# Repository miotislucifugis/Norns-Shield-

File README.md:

A (very minor) rework of Norns Shield 210330 that adds TRS (type A) Midi IN and OUT.

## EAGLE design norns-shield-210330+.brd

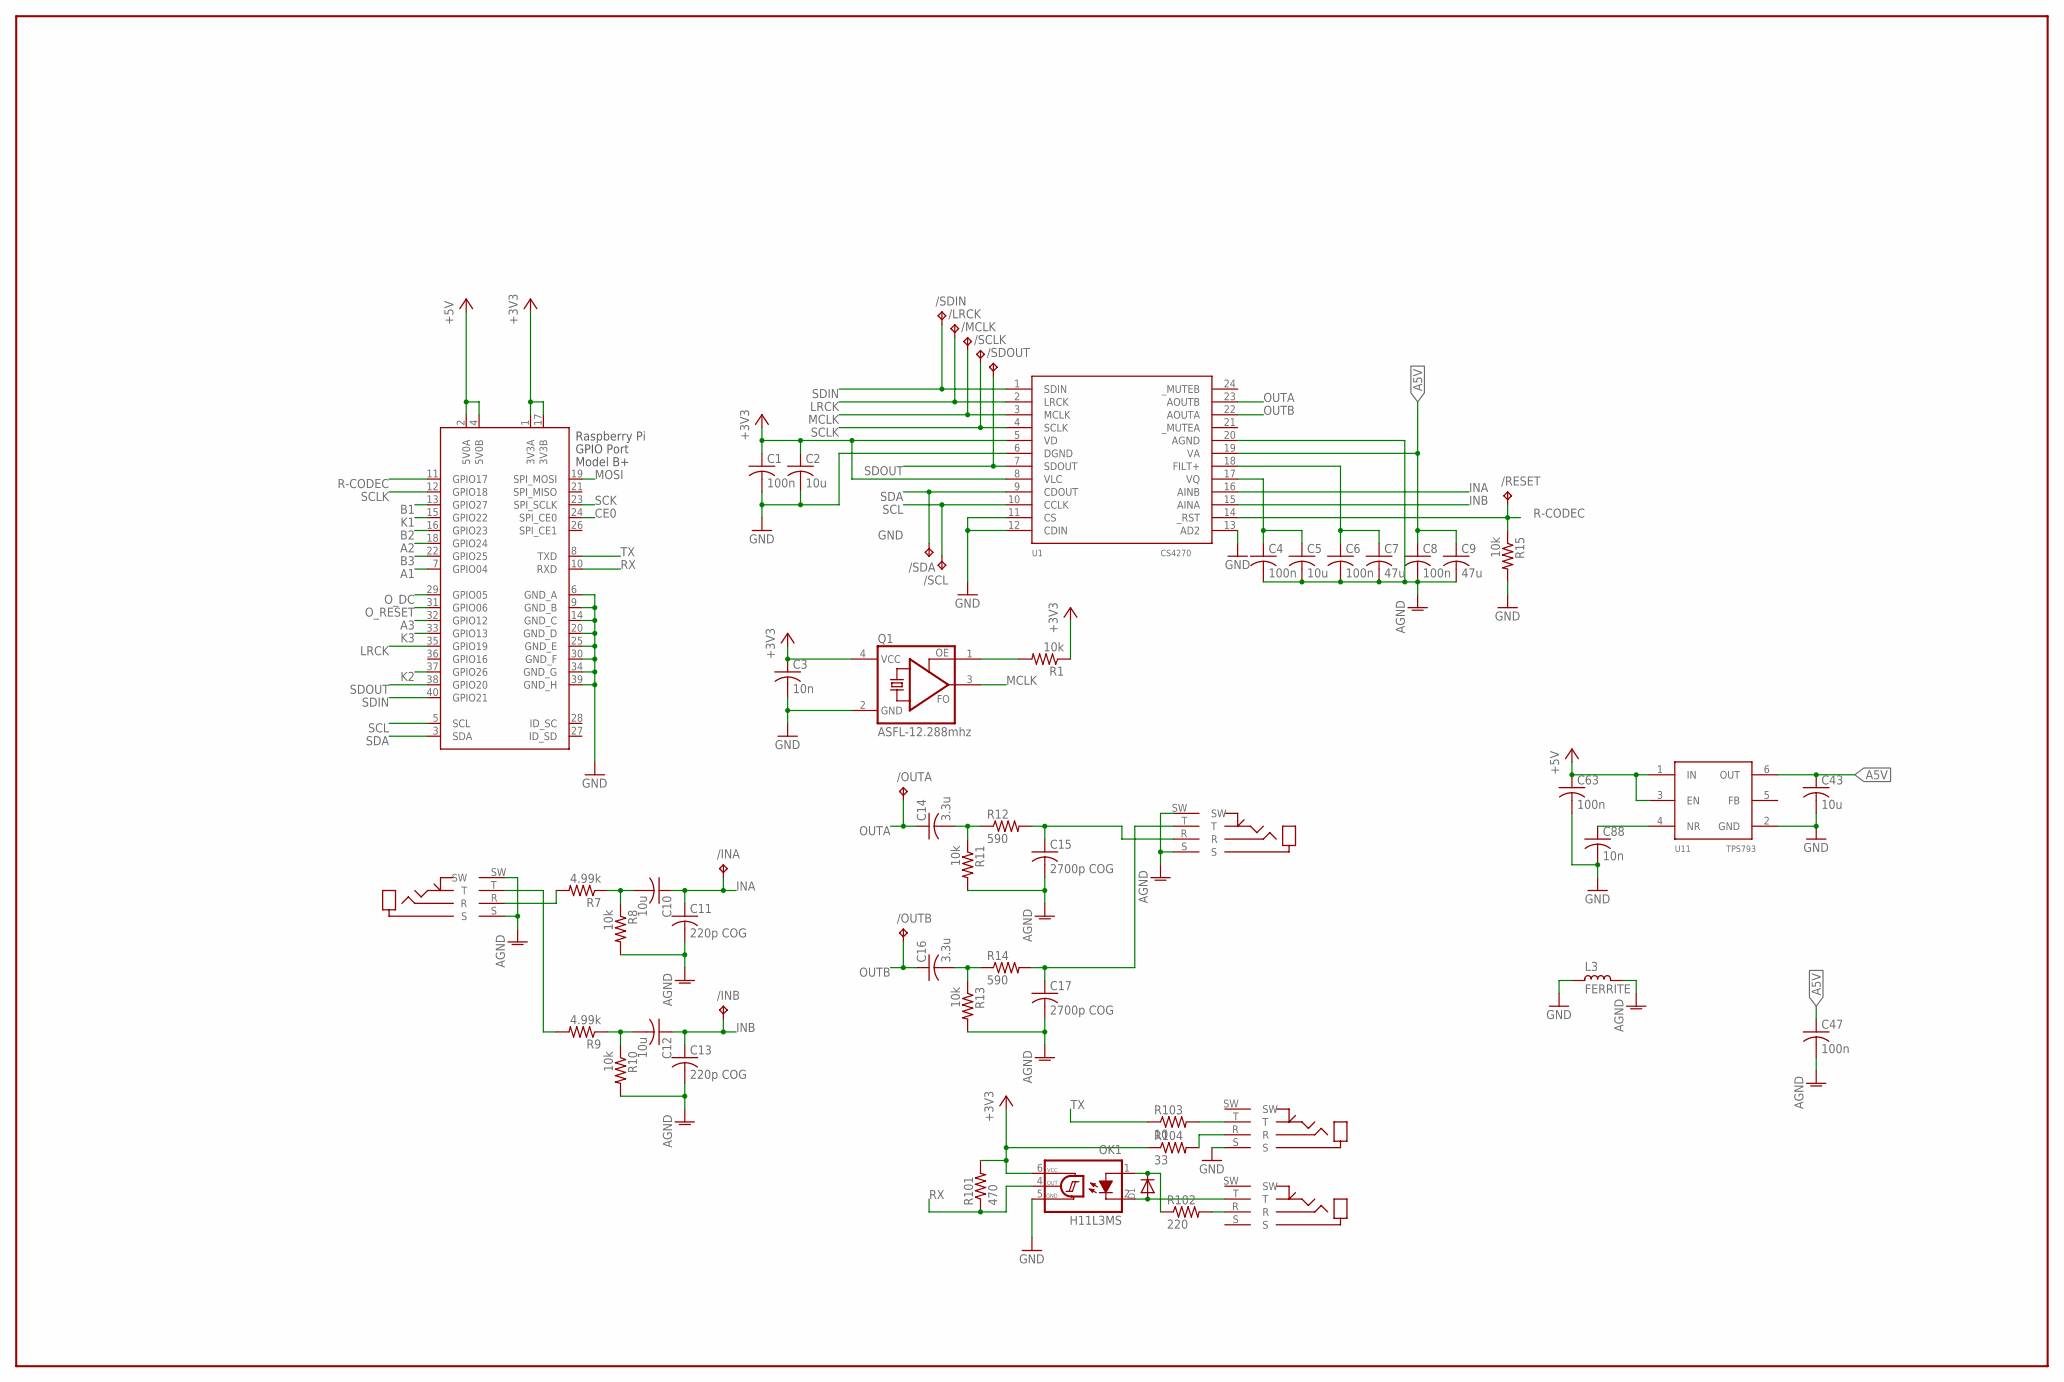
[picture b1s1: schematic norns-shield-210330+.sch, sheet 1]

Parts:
/INA: TPTP12R; TP12R
/INB: TPTP12R; TP12R
/LRCK: TPTP12R; TP12R
/MCLK: TPTP12R; TP12R
/OUTA: TPTP12R; TP12R
/OUTB: TPTP12R; TP12R
/RESET: TPTP12R; TP12R
/SCL: TPTP12R; TP12R
/SCLK: TPTP12R; TP12R
/SDA: TPTP12R; TP12R
/SDIN: TPTP12R; TP12R
/SDOUT: TPTP12R; TP12R
C1, C4, C6, C8, C47, C63: 100n; C0603
C2, C5, C10, C12, C43: 10u; C0805
C3, C88: 10n; C0603
C7, C9: 47u; C1206
C11, C13: 220p COG; C0603
C14, C16: 3.3u; C0805
C15, C17: 2700p COG; C0603
D1: DIODESOD-323F; SOD-323F
J-IN: JACK-TRS-SW; JACK4832.2330
J-OUT, J-OUT1, J-OUT2: JACK-TRS-SW; JACK4832.2330
L3: FERRITE; L0805
OK1: H11L3MS; DIL6-SMD
Q1: ASFL-12.288mhz; ASF
R1, R8, R10, R11, R13, R15: 10k; R0603
R7, R9: 4.99k; R0603
R12, R14: 590; R0603
R101: 470; R0603
R102: 220; R0603
R103: 10; R0603
R104: 33; R0603
U1: CS4270; TSSOP24
U11: TPS793; SSOP6
X1: RASPI_BOARD_B+#_E3; RASPI_BOARD_B+_EDGES_3DRILL

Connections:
+3V3: C1.1, C2.1, C3.1, OK1.6 (VCC), Q1.4 (VCC), R1.1, R101.2, R104.1, U1.5 (VD), U1.8 (VLC), X1.1 (3V3A), X1.17 (3V3B); also elsewhere on the board
+5V: C63.1, U11.1 (IN), U11.3 (EN), X1.2 (5V0A), X1.4 (5V0B)
A1: X1.7 (GPIO04); also elsewhere on the board
A2: X1.18 (GPIO24); also elsewhere on the board
A3: X1.32 (GPIO12); also elsewhere on the board
A5V: C8.1, C9.1, C43.1, C47.1, U1.19 (VA), U11.6 (OUT)
AGND: C4.2, C5.2, C6.2, C7.2, C8.2, C9.2, C11.2, C13.2, C15.2, C17.2, C47.2, J-IN.S, J-IN.SW, J-OUT.S, J-OUT.SW, L3.1, R8.2, R10.2, R11.2, R13.2, U1.20 (AGND)
B1: X1.13 (GPIO27); also elsewhere on the board
B2: X1.16 (GPIO23); also elsewhere on the board
B3: X1.22 (GPIO25); also elsewhere on the board
CE0: X1.24 (SPI_CE0); also elsewhere on the board
GND: C1.2, C2.2, C3.2, C43.2, C63.2, C88.2, J-OUT1.S, L3.2, OK1.5 (GND), Q1.2 (GND), R15.2, U1.6 (DGND), U1.11 (CS), U1.12 (CDIN), U1.13 (AD2), U11.2 (GND), X1.6 (GND_A), X1.9 (GND_B), X1.14 (GND_C), X1.20 (GND_D), X1.25 (GND_E), X1.30 (GND_F), X1.34 (GND_G), X1.39 (GND_H); also elsewhere on the board
INA: /INA.TP, C10.1, C11.1, U1.16 (AINB)
INB: /INB.TP, C12.1, C13.1, U1.15 (AINA)
K1: X1.15 (GPIO22); also elsewhere on the board
K2: X1.37 (GPIO26); also elsewhere on the board
K3: X1.33 (GPIO13); also elsewhere on the board
LRCK: /LRCK.TP, U1.2 (LRCK), X1.35 (GPIO19)
MCLK: /MCLK.TP, Q1.3 (FO), U1.3 (MCLK)
MOSI: X1.19 (SPI_MOSI); also elsewhere on the board
unnamed: Q1.1 (OE), R1.2
unnamed: C4.1, C5.1, U1.17 (VQ)
unnamed: C6.1, C7.1, U1.18 (FILT+)
unnamed: J-IN.R, R7.2
unnamed: J-OUT2.R, R102.2
unnamed: C10.2, R7.1, R8.1
unnamed: C12.2, R9.1, R10.1
unnamed: D1.A, J-OUT2.T, OK1.2 (C)
unnamed: J-IN.T, R9.2
unnamed: C16.2, R13.1, R14.1
unnamed: C14.2, R11.1, R12.1
unnamed: C15.1, J-OUT.R, R12.2
unnamed: C17.1, J-OUT.T, R14.2
unnamed: D1.C, OK1.1 (A), R102.1
unnamed: J-OUT1.T, R103.2
unnamed: J-OUT1.R, R104.2
unnamed: C88.1, U11.4 (NR)
OUTA: /OUTA.TP, C14.1, U1.23 (AOUTB)
OUTB: /OUTB.TP, C16.1, U1.22 (AOUTA)
O_DC: X1.29 (GPIO05); also elsewhere on the board
O_RESET: X1.31 (GPIO06); also elsewhere on the board
R-CODEC: /RESET.TP, R15.1, U1.14 (_RST), X1.11 (GPIO17)
RX: OK1.4 (OUT), R101.1, X1.10 (RXD)
SCK: X1.23 (SPI_SCLK); also elsewhere on the board
SCL: /SCL.TP, U1.10 (CCLK), X1.5 (SCL)
SCLK: /SCLK.TP, U1.4 (SCLK), X1.12 (GPIO18)
SDA: /SDA.TP, U1.9 (CDOUT), X1.3 (SDA)
SDIN: /SDIN.TP, U1.1 (SDIN), X1.40 (GPIO21)
SDOUT: /SDOUT.TP, U1.7 (SDOUT), X1.38 (GPIO20)
TX: R103.1, X1.8 (TXD)

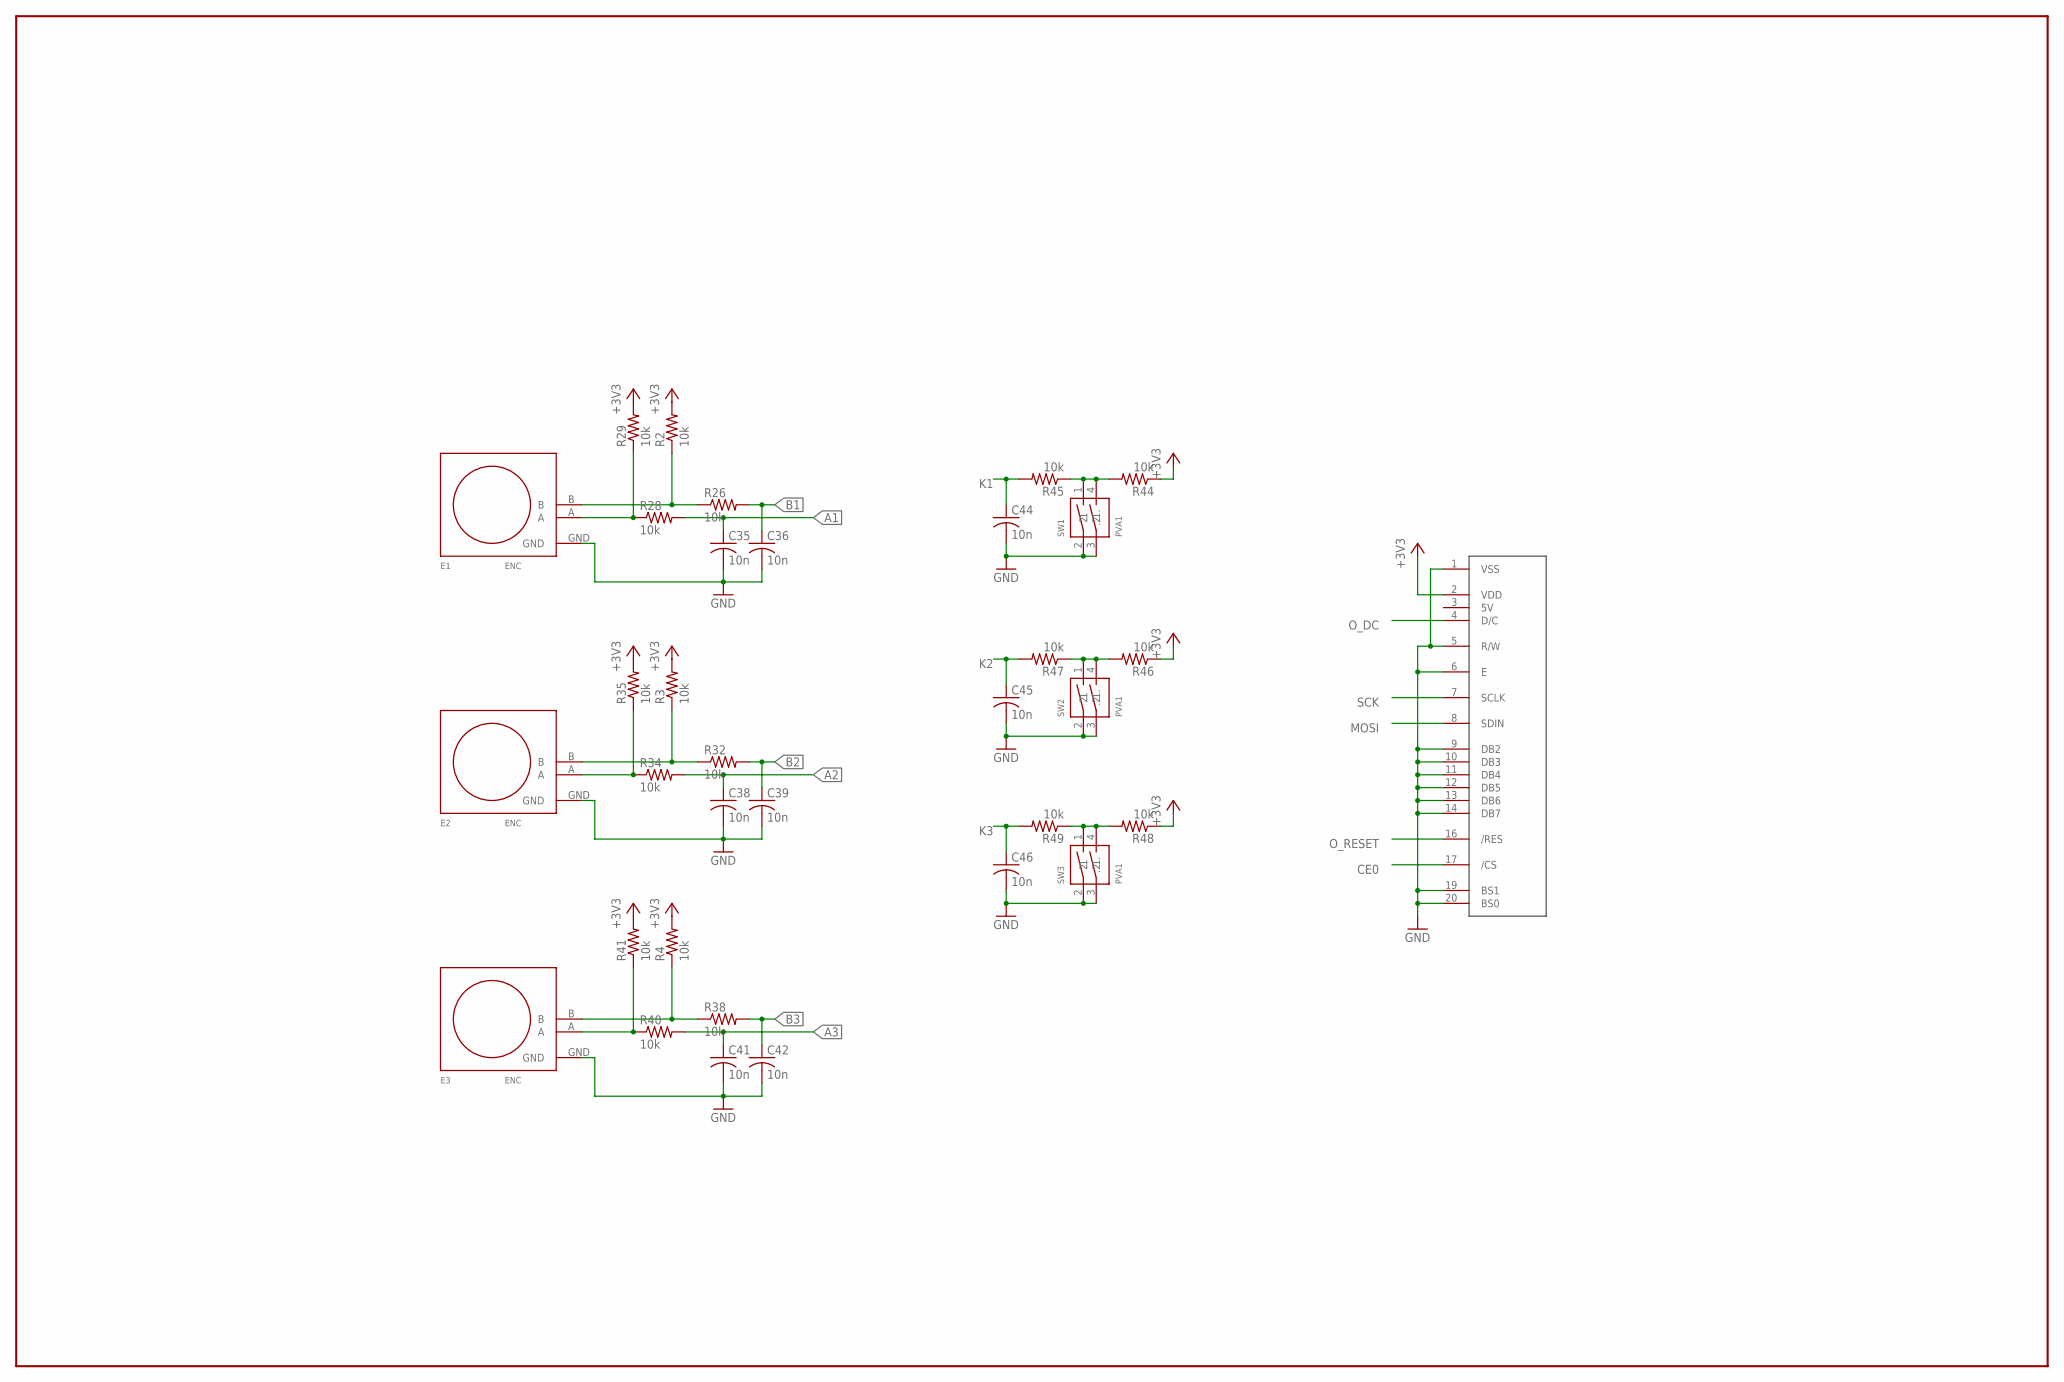
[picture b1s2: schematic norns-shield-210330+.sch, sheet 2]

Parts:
C35, C36, C38, C39, C41, C42, C44, C45, C46: 10n; C0603
E1, E2, E3: ENC; PEC11RN
R2, R3, R4, R26, R28, R29, R32, R34, R35, R38, R40, R41, R44, R45, R46, R47, R48, R49: 10k; R0603
SW1, SW2, SW3: PVA1
U$1: OLED128X64; OLED-ALEPH

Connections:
+3V3: R2.2, R3.2, R4.2, R29.2, R35.2, R41.2, R44.1, R46.1, R48.1, U$1.2 (VDD); also elsewhere on the board
A1: C35.1, R28.2; also elsewhere on the board
A2: C38.1, R34.2; also elsewhere on the board
A3: C41.1, R40.2; also elsewhere on the board
B1: C36.1, R26.2; also elsewhere on the board
B2: C39.1, R32.2; also elsewhere on the board
B3: C42.1, R38.2; also elsewhere on the board
CE0: U$1.17 (/CS); also elsewhere on the board
GND: C35.2, C36.2, C38.2, C39.2, C41.2, C42.2, C44.2, C45.2, C46.2, E1.GND, E2.GND, E3.GND, SW1.2 (1), SW1.3 (1.), SW2.2 (1), SW2.3 (1.), SW3.2 (1), SW3.3 (1.), U$1.1 (VSS), U$1.5 (R/W), U$1.6 (E), U$1.9 (DB2), U$1.10 (DB3), U$1.11 (DB4), U$1.12 (DB5), U$1.13 (DB6), U$1.14 (DB7), U$1.19 (BS1), U$1.20 (BS0); also elsewhere on the board
K1: C44.1, R45.2; also elsewhere on the board
K2: C45.1, R47.2; also elsewhere on the board
K3: C46.1, R49.2; also elsewhere on the board
MOSI: U$1.8 (SDIN); also elsewhere on the board
unnamed: R44.2, R45.1, SW1.1 (2), SW1.4 (.2)
unnamed: R46.2, R47.1, SW2.1 (2), SW2.4 (.2)
unnamed: R48.2, R49.1, SW3.1 (2), SW3.4 (.2)
unnamed: E1.A, R28.1, R29.1
unnamed: E1.B, R2.1, R26.1
unnamed: E2.B, R3.1, R32.1
unnamed: E2.A, R34.1, R35.1
unnamed: E3.B, R4.1, R38.1
unnamed: E3.A, R40.1, R41.1
O_DC: U$1.4 (D/C); also elsewhere on the board
O_RESET: U$1.16 (/RES); also elsewhere on the board
SCK: U$1.7 (SCLK); also elsewhere on the board

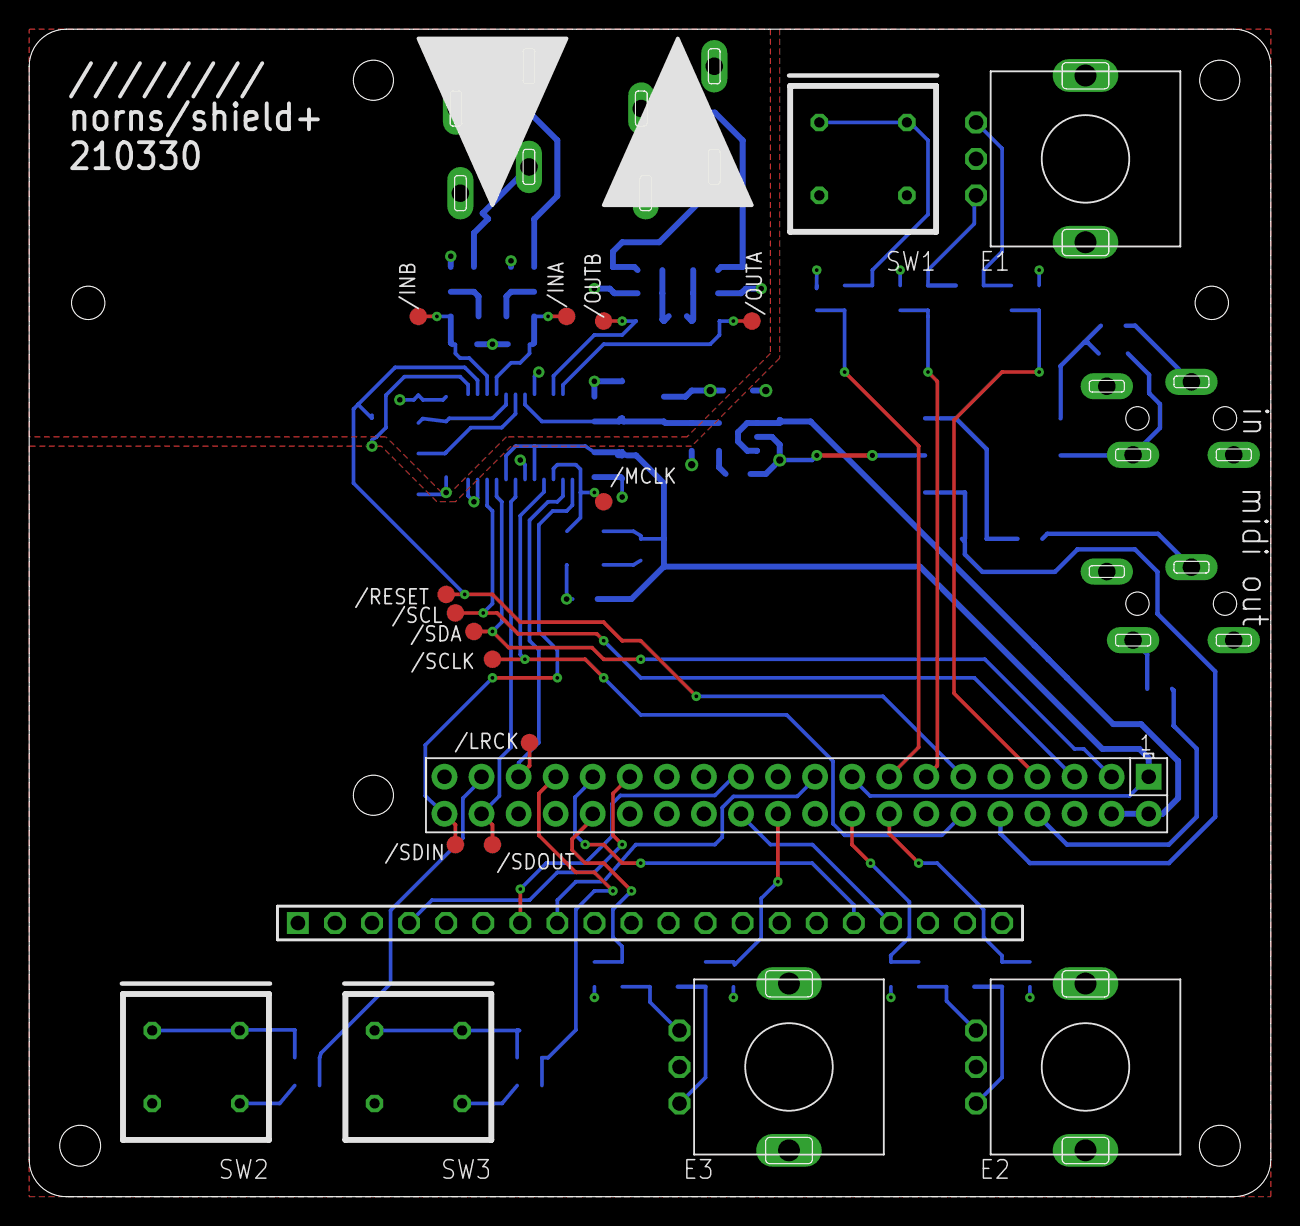
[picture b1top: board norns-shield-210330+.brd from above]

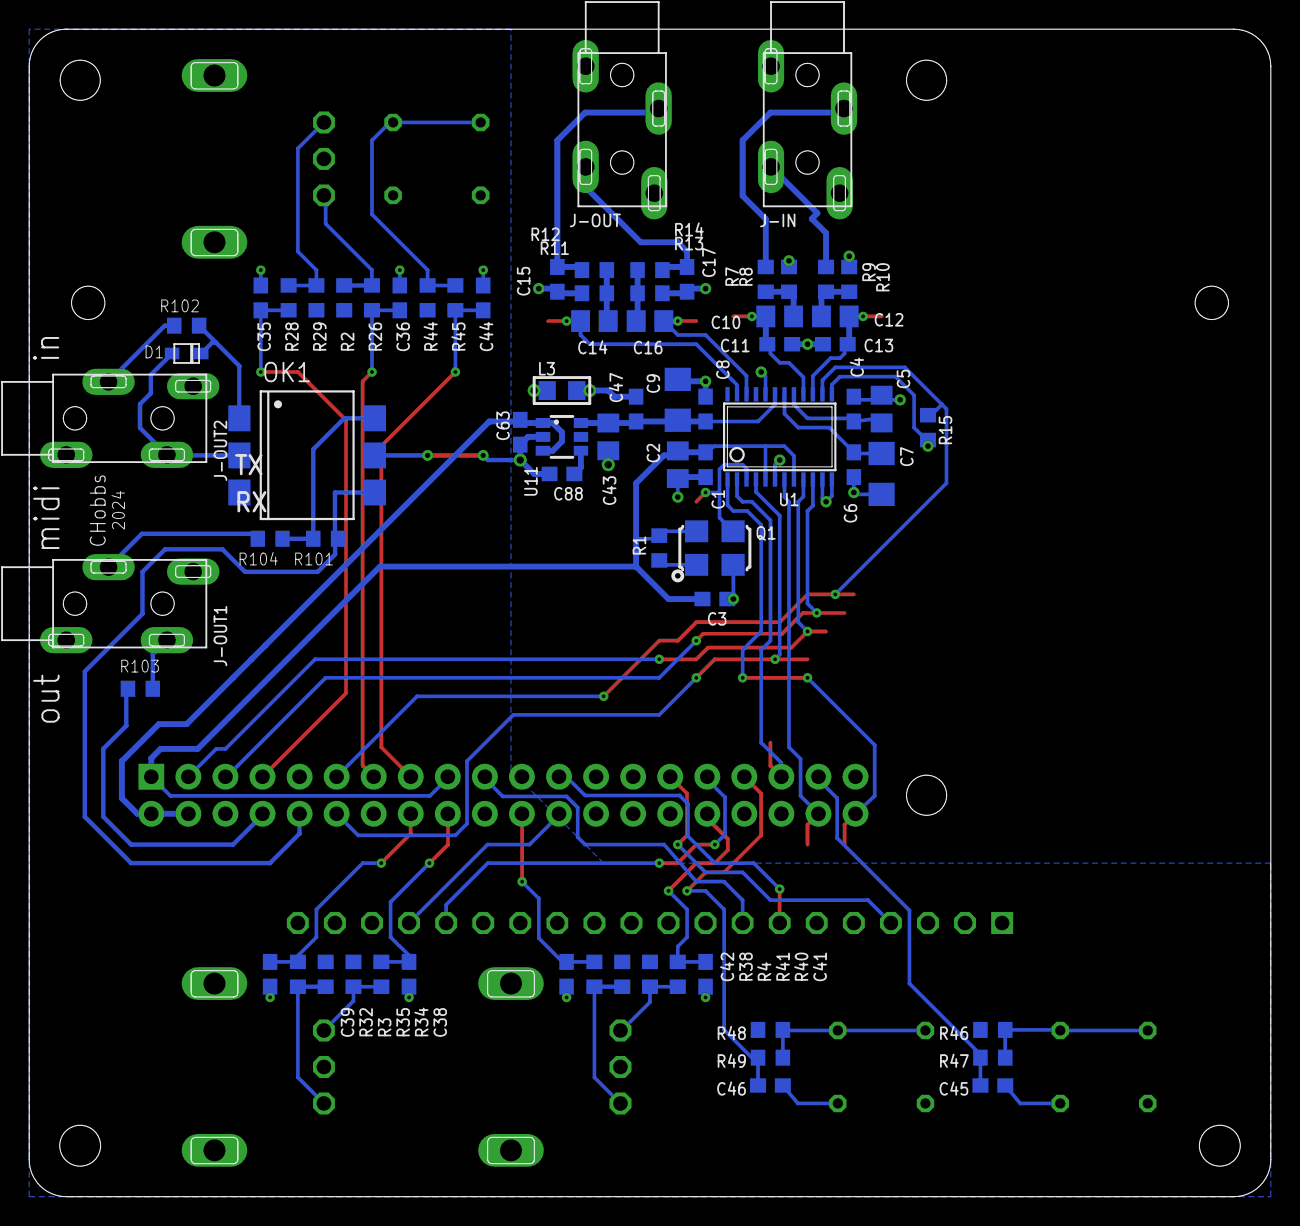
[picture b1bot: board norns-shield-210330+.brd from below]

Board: 2 copper layers, 85.1 x 80.0 mm, 92 parts (72 on the bottom side), 59 nets.

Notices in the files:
parts and their libraries:
rc-master-smd: Copyright (C) 2007-2008, Bob Starr
SparkFun-Aesthetics: Licensing: Creative Commons ShareAlike 4.0 International - https://creativecommons.org/licenses/by-sa/4.0
